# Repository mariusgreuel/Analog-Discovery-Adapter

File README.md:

# Pin Header Adapter for Analog Discovery USB Oscilloscope

I own an [Analog Discovery 2](https://digilent.com/shop/analog-discovery-2-100ms-s-usb-oscilloscope-logic-analyzer-and-variable-power-supply/) USB oscilloscope and logic analyzer from [Digilent](https://digilent.com/), which is a fantastic little device for all sorts of Arduino style activity. To connect the Analog Discovery to your devices, the flywire cables works very well.

However, I tend to use longer cables, and I rarely have all cables connected. To connect cables individually, I found it easier to connect them from the top, so I build a little adapter that switches orientation of the pin header connector. As a bonus, I added a second connector, so you no longer need a V-cable if you have more than one connection on a single pin.

The rendered image of the adapter looks like this:

## KiCad schematic and PCB

You can find the KiCad schematic and PCB layout files in the [PCB folder](./pcb).

## Gerber Files

If you just want to build an adapter yourself, you can use my [Gerber Plots](./pcb/discovery_adapter_gerber.zip) and send them to your favorite PCB manufacturer.

## License

The Pin Header Adapter schematic and PCB layout is released under the GNU GPLv3.

Copyright 2021 Marius Greuel.

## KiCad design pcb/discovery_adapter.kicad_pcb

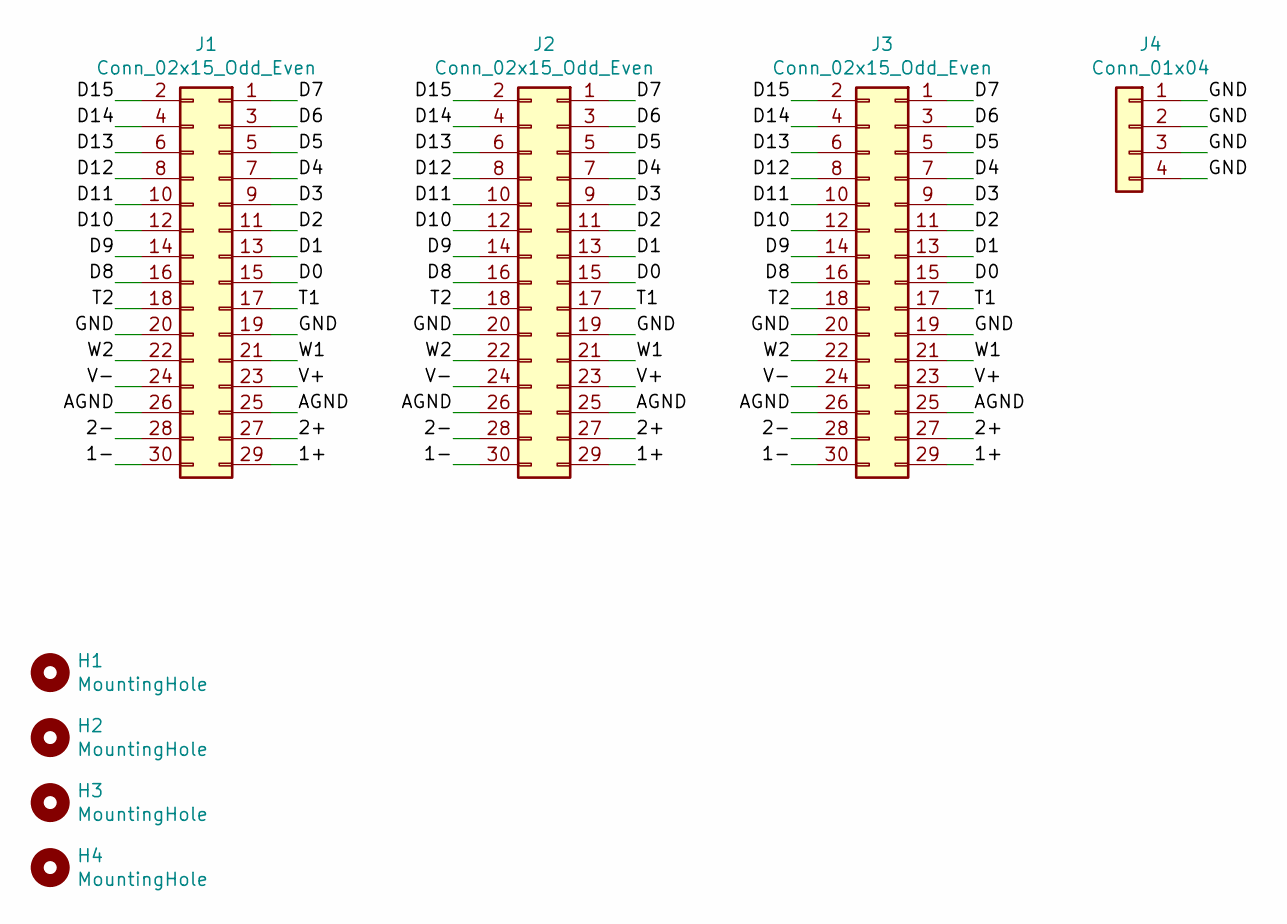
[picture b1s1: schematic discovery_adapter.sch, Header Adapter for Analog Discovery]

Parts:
H1, H2, H3, H4: MountingHole; MountingHole_3.2mm_M3
J1: Conn_02x15_Odd_Even; PinSocket_2x15_P2.54mm_Horizontal
J2, J3: Conn_02x15_Odd_Even; PinHeader_2x15_P2.54mm_Vertical
J4: Conn_01x04; PinHeader_1x04_P2.54mm_Vertical

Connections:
/1+: J1.29, J2.29, J3.29
/1-: J1.30, J2.30, J3.30
/2+: J1.27, J2.27, J3.27
/2-: J1.28, J2.28, J3.28
/AGND: J1.25, J1.26, J2.25, J2.26, J3.25, J3.26
/D0: J1.15, J2.15, J3.15
/D1: J1.13, J2.13, J3.13
/D2: J1.11, J2.11, J3.11
/D3: J1.9, J2.9, J3.9
/D4: J1.7, J2.7, J3.7
/D5: J1.5, J2.5, J3.5
/D6: J1.3, J2.3, J3.3
/D7: J1.1, J2.1, J3.1
/D8: J1.16, J2.16, J3.16
/D9: J1.14, J2.14, J3.14
/D10: J1.12, J2.12, J3.12
/D11: J1.10, J2.10, J3.10
/D12: J1.8, J2.8, J3.8
/D13: J1.6, J2.6, J3.6
/D14: J1.4, J2.4, J3.4
/D15: J1.2, J2.2, J3.2
/GND: J1.19, J1.20, J2.19, J2.20, J3.19, J3.20, J4.1, J4.2, J4.3, J4.4
/T1: J1.17, J2.17, J3.17
/T2: J1.18, J2.18, J3.18
/V+: J1.23, J2.23, J3.23
/V-: J1.24, J2.24, J3.24
/W1: J1.21, J2.21, J3.21
/W2: J1.22, J2.22, J3.22

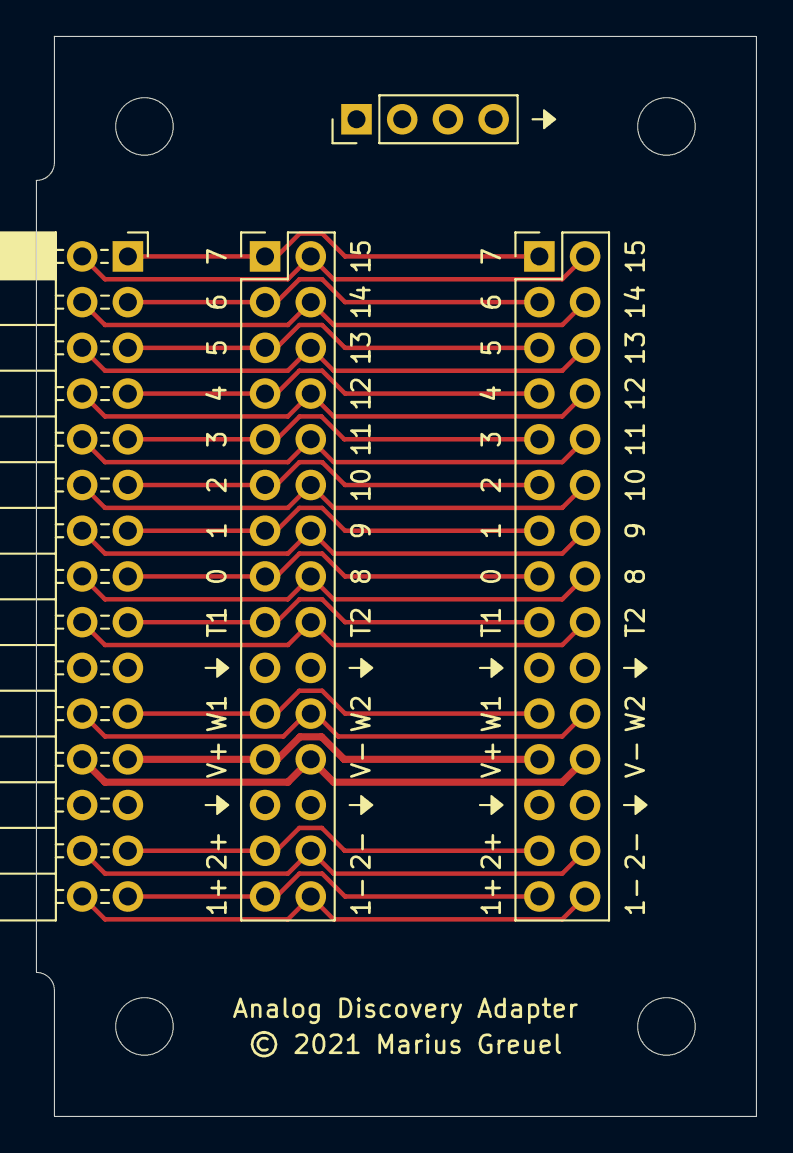
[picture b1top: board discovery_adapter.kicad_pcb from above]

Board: 2 copper layers, 40.0 x 60.0 mm, 8 parts (0 on the bottom side), 28 nets.

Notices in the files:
pcb/discovery_adapter.kicad_pcb:
© 2021 Marius Greuel
